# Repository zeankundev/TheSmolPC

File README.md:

# The Smol PC
An obscure, RP2350B-based computer motherboard on a smol form factor that you will think it's cute. And another absurd project I'm working on.

In essence, it's basically Adafruit's Fruit Jam but better and improved (fixes major issues lol, adafruit pls fix ur routing)

## Features
- [x] USB 1.1 with both power & data, up to 2x USB-A ports and 1x USB-C port, HID-compliant
- [x] SD Card as storage medium
- [x] HDMI/DVI video output
- [x] Big amount of flash and PSRAM (flash will be around 16MB) for a microcontroller
- [x] I2S/PCM audio output via a standard 3.5mm jack
- [ ] **Out of the box firmware boot** - this means that you can run any UEFI-like firmware for any OS you want to run, or you can use a stock firmware, or flash a generic firmware as if you were flashing on a normal RP2350 (maybe ?)
- [x] Debug Probe-compatible debug ports (Raspberry Pi Debug Probe)
- [x] Built-in WiFi support (ESP32-C3)

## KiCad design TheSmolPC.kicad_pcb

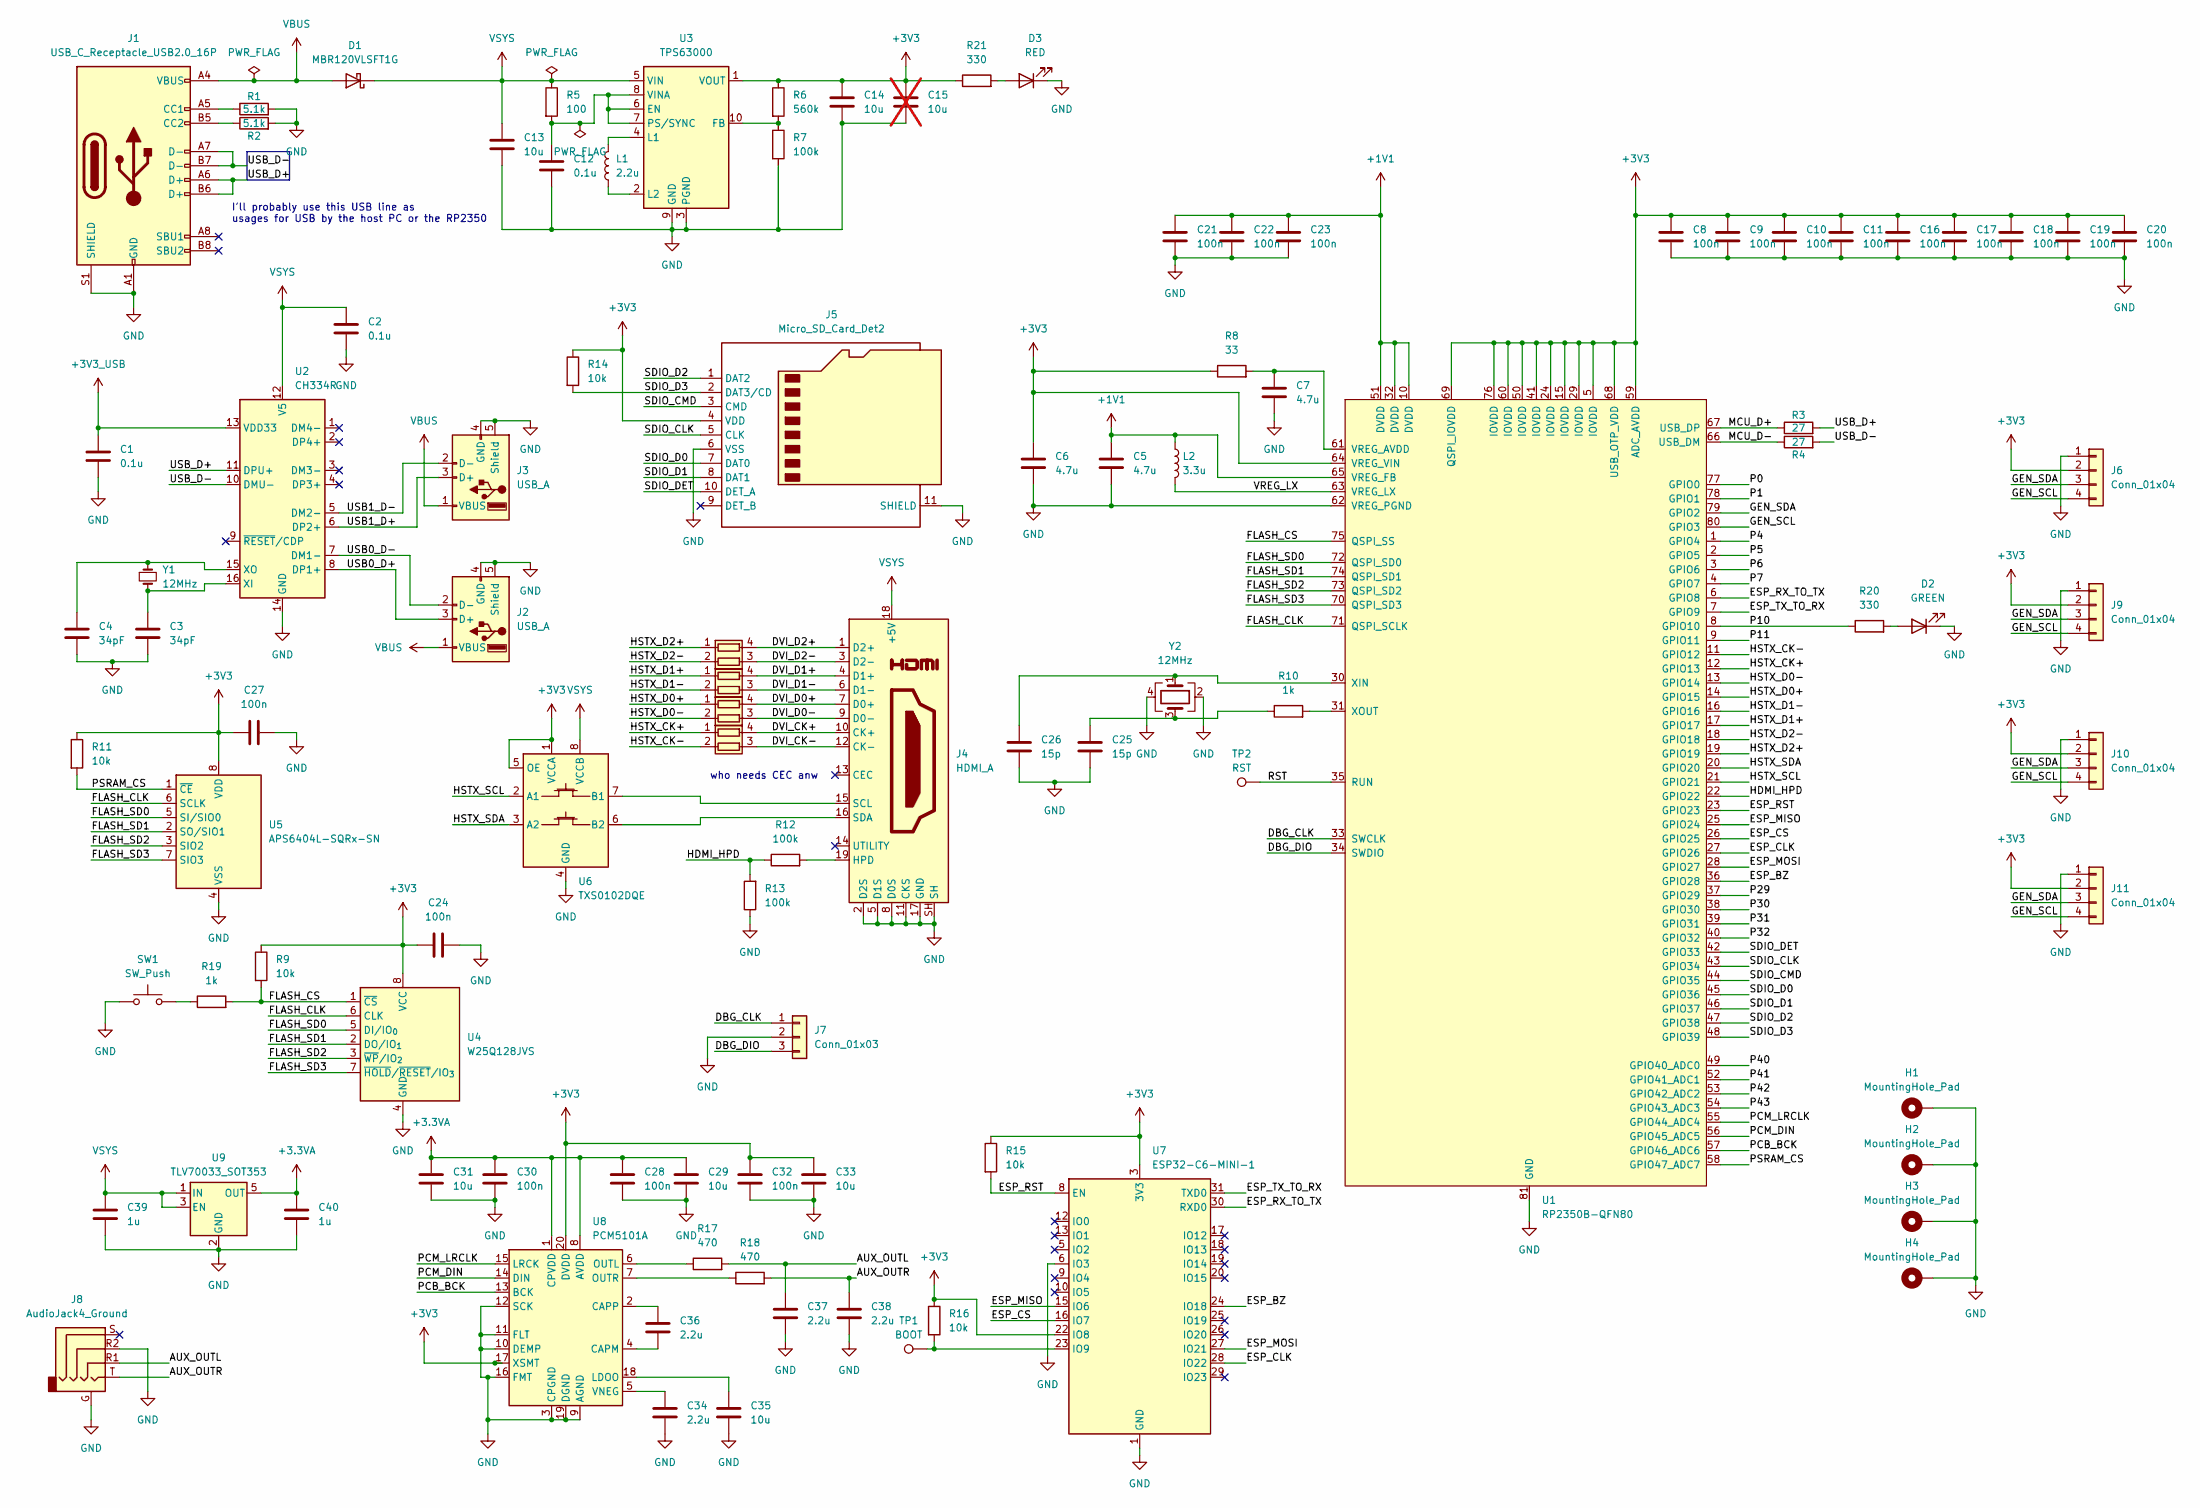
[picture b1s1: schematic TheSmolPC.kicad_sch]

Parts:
C1, C2, C12: 0.1u; C_0402_1005Metric
C3, C4: 34pF; C_0402_1005Metric
C5, C6, C7: 4.7u; C_0402_1005Metric
C8, C9, C10, C11, C16, C17, C18, C19, C20, C21, C22, C23, C24, C27, C28, C30, C32: 100n; C_0402_1005Metric
C13, C14: 10u; C_0805_2012Metric
C15: 10u; C_0805_2012Metric; not fitted
C25, C26: 15p; C_0402_1005Metric
C29, C31, C33, C35: 10u; C_0402_1005Metric
C34, C36, C37, C38: 2.2u; C_0402_1005Metric
C39, C40: 1u; C_0402_1005Metric
D1: MBR120VLSFT1G; D_SOD-123F
D2: GREEN; LED_0402_1005Metric
D3: RED; LED_0402_1005Metric
H1, H2, H3, H4: MountingHole_Pad; MountingHole_3.2mm_M3_DIN965_Pad
J1: USB_C_Receptacle_USB2.0_16P; USB_C_Receptacle_GCT_USB4105-xx-A_16P_TopMnt_Horizontal
J2, J3: USB_A; USB_A_Receptacle_GCT_USB1046
J4: HDMI_A; HDMI_A_Molex_208658-1001_Horizontal
J5: Micro_SD_Card_Det2; microSD_HC_Hirose_DM3D-SF
J6, J9, J10, J11: Conn_01x04; JST_SH_SM04B-SRSS-TB_1x04-1MP_P1.00mm_Horizontal
J7: Conn_01x03; JST_SH_SM03B-SRSS-TB_1x03-1MP_P1.00mm_Horizontal
J8: AudioJack4_Ground; Jack_3.5mm_KoreanHropartsElec_PJ-320D-4A_Horizontal
L1: 2.2u; L_Changjiang_FNR3015S
L2: 3.3u; L_Murata_DFE201610P
R1, R2: 5.1k; R_0402_1005Metric
R3, R4: 27; R_0402_1005Metric
R5: 100; R_0402_1005Metric
R6: 560k; R_0402_1005Metric
R7, R12, R13: 100k; R_0402_1005Metric
R8: 33; R_0402_1005Metric
R9, R11, R14, R15, R16: 10k; R_0402_1005Metric
R10, R19: 1k; R_0402_1005Metric
R17, R18: 470; R_0402_1005Metric
R20, R21: 330; R_0402_1005Metric
RN1, RN2, RN3, RN4: 220; R_Array_Convex_2x0402
SW1: SW_Push; SW_Push_1P1T_NO_Vertical_Wuerth_434133025816
TP1: BOOT; TestPoint_Pad_D1.0mm
TP2: RST; TestPoint_Pad_D1.0mm
U1: RP2350B-QFN80; QFN-80-1EP_10x10mm_P0.4mm_EP3.4x3.4mm_ThermalVias
U2: CH334R; QSOP-16_3.9x4.9mm_P0.635mm
U3: TPS63000; Texas_DRC0010J_ThermalVias
U4: W25Q128JVS; SOIC-8_5.3x5.3mm_P1.27mm
U5: APS6404L-SQRx-SN; SOIC-8_3.9x4.9mm_P1.27mm
U6: TXS0102DQE; X2SON-8_1.4x1mm_P0.35mm
U7: ESP32-C6-MINI-1
U8: PCM5101A; TSSOP-20_4.4x6.5mm_P0.65mm
U9: TLV70033_SOT353; SOT-353_SC-70-5
Y1: 12MHz; Crystal_SMD_Abracon_ABM3-2Pin_5.0x3.2mm
Y2: 12MHz; Crystal_SMD_3225-4Pin_3.2x2.5mm

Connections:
+1V1: C5.1, C21.1, C22.1, C23.1, L2.1, U1.10 (DVDD), U1.32 (DVDD), U1.51 (DVDD), U1.65 (VREG_FB)
+3.3VA: C28.1, C29.1, C30.1, C31.1, C40.1, U8.1 (CPVDD), U8.8 (AVDD), U9.5 (OUT)
+3V3: C6.1, C8.1, C9.1, C10.1, C11.1, C14.1, C15.1, C16.1, C17.1, C18.1, C19.1, C20.1, C24.1, C27.1, C32.1, C33.1, J5.4 (VDD), J6.2, J9.2, J10.2, J11.2, R6.1, R8.1, R9.1, R11.1, R14.1, R15.1, R16.1, R21.1, U1.5 (IOVDD), U1.15 (IOVDD), U1.24 (IOVDD), U1.29 (IOVDD), U1.41 (IOVDD), U1.50 (IOVDD), U1.59 (ADC_AVDD), U1.60 (IOVDD), U1.64 (VREG_VIN), U1.68 (USB_OTP_VDD), U1.69 (QSPI_IOVDD), U1.76 (IOVDD), U3.1 (VOUT), U4.8 (VCC), U5.8 (VDD), U6.1 (VCCA), U6.5 (OE), U7.3 (3V3), U7.22 (IO8), U8.17 (XSMT), U8.20 (DVDD)
+3V3_USB: C1.1, U2.13 (VDD33)
/AUX_OUTL: C37.1, J8.R1, R17.2
/AUX_OUTR: C38.1, J8.T, R18.2
/DBG_CLK: J7.1, U1.33 (SWCLK)
/DBG_DIO: J7.3, U1.34 (SWDIO)
/DVI_CK+: J4.10 (CK+), RN4.4 (R1.2)
/DVI_CK-: J4.12 (CK-), RN4.3 (R2.2)
/DVI_D0+: J4.7 (D0+), RN3.4 (R1.2)
/DVI_D0-: J4.9 (D0-), RN3.3 (R2.2)
/DVI_D1+: J4.4 (D1+), RN2.4 (R1.2)
/DVI_D1-: J4.6 (D1-), RN2.3 (R2.2)
/DVI_D2+: J4.1 (D2+), RN1.4 (R1.2)
/DVI_D2-: J4.3 (D2-), RN1.3 (R2.2)
/ESP_BZ: U1.36 (GPIO28), U7.24 (IO18)
/ESP_CLK: U1.27 (GPIO26), U7.28 (IO22)
/ESP_CS: U1.26 (GPIO25), U7.16 (IO7)
/ESP_MISO: U1.25 (GPIO24), U7.15 (IO6)
/ESP_MOSI: U1.28 (GPIO27), U7.27 (IO21)
/ESP_RST: R15.2, U1.23 (GPIO23), U7.8 (EN)
/ESP_RX_TO_TX: U1.6 (GPIO8), U7.30 (RXD0)
/ESP_TX_TO_RX: U1.7 (GPIO9), U7.31 (TXD0)
/FLASH_CLK: U1.71 (QSPI_SCLK), U4.6 (CLK), U5.6 (SCLK)
/FLASH_CS: R9.2, R19.2, U1.75 (QSPI_SS), U4.1 (~CS)
/FLASH_SD0: U1.72 (QSPI_SD0), U4.5 (DI/IO_{0}), U5.5 (SI/SIO0)
/FLASH_SD1: U1.74 (QSPI_SD1), U4.2 (DO/IO_{1}), U5.2 (SO/SIO1)
/FLASH_SD2: U1.73 (QSPI_SD2), U4.3 (~WP/IO_{2}), U5.3 (SIO2)
/FLASH_SD3: U1.70 (QSPI_SD3), U4.7 (~HOLD/~RESET/IO_{3}), U5.7 (SIO3)
/GEN_SCL: J6.4, J9.4, J10.4, J11.4, U1.80 (GPIO3)
/GEN_SDA: J6.3, J9.3, J10.3, J11.3, U1.79 (GPIO2)
/HDMI_HPD: R12.1, R13.2, U1.22 (GPIO22)
/HSTX_CK+: RN4.1 (R1.1), U1.12 (GPIO13)
/HSTX_CK-: RN4.2 (R2.1), U1.11 (GPIO12)
/HSTX_D0+: RN3.1 (R1.1), U1.14 (GPIO15)
/HSTX_D0-: RN3.2 (R2.1), U1.13 (GPIO14)
/HSTX_D1+: RN2.1 (R1.1), U1.17 (GPIO17)
/HSTX_D1-: RN2.2 (R2.1), U1.16 (GPIO16)
/HSTX_D2+: RN1.1 (R1.1), U1.19 (GPIO19)
/HSTX_D2-: RN1.2 (R2.1), U1.18 (GPIO18)
/HSTX_SCL: U1.21 (GPIO21), U6.2 (A1)
/HSTX_SDA: U1.20 (GPIO20), U6.3 (A2)
/MCU_D+: R3.1, U1.67 (USB_DP)
/MCU_D-: R4.1, U1.66 (USB_DM)
/P0: U1.77 (GPIO0)
/P1: U1.78 (GPIO1)
/P4: U1.1 (GPIO4)
/P5: U1.2 (GPIO5)
/P6: U1.3 (GPIO6)
/P7: U1.4 (GPIO7)
/P10: R20.1, U1.8 (GPIO10)
/P11: U1.9 (GPIO11)
/P29: U1.37 (GPIO29)
/P30: U1.38 (GPIO30)
/P31: U1.39 (GPIO31)
/P32: U1.40 (GPIO32)
/P40: U1.49 (GPIO40_ADC0)
/P41: U1.52 (GPIO41_ADC1)
/P42: U1.53 (GPIO42_ADC2)
/P43: U1.54 (GPIO43_ADC3)
/PCB_BCK: U1.57 (GPIO46_ADC6), U8.13 (BCK)
/PCM_DIN: U1.56 (GPIO45_ADC5), U8.14 (DIN)
/PCM_LRCLK: U1.55 (GPIO44_ADC4), U8.15 (LRCK)
/PSRAM_CS: R11.2, U1.58 (GPIO47_ADC7), U5.1 (~CE)
/RST: TP2.1, U1.35 (RUN)
/SDIO_CLK: J5.5 (CLK), U1.43 (GPIO34)
/SDIO_CMD: J5.3 (CMD), U1.44 (GPIO35)
/SDIO_D0: J5.7 (DAT0), U1.45 (GPIO36)
/SDIO_D1: J5.8 (DAT1), U1.46 (GPIO37)
/SDIO_D2: J5.1 (DAT2), U1.47 (GPIO38)
/SDIO_D3: J5.2 (DAT3/CD), R14.2, U1.48 (GPIO39)
/SDIO_DET: J5.10 (DET_A), U1.42 (GPIO33)
/USB0_D+: J2.3 (D+), U2.8 (DP1+)
/USB0_D-: J2.2 (D-), U2.7 (DM1-)
/USB1_D+: J3.3 (D+), U2.6 (DP2+)
/USB1_D-: J3.2 (D-), U2.5 (DM2-)
/USB_D+: J1.A6 (D+), J1.B6 (D+), R3.2, U2.11 (DPU+)
/USB_D-: J1.A7 (D-), J1.B7 (D-), R4.2, U2.10 (DMU-)
/VREG_LX: L2.2, U1.63 (VREG_LX)
GND: C1.2, C2.2, C3.2, C4.2, C5.2, C6.2, C7.2, C8.2, C9.2, C10.2, C11.2, C12.2, C13.2, C14.2, C15.2, C16.2, C17.2, C18.2, C19.2, C20.2, C21.2, C22.2, C23.2, C24.2, C25.2, C26.2, C27.2, C28.2, C29.2, C30.2, C31.2, C32.2, C33.2, C34.2, C35.2, C37.2, C38.2, C39.2, C40.2, D2.1 (K), D3.1 (K), H1.1, H2.1, H3.1, H4.1, J1.A1 (GND), J1.A12 (GND), J1.B1 (GND), J1.B12 (GND), J1.S1 (SHIELD), J2.4 (GND), J2.5 (Shield), J3.4 (GND), J3.5 (Shield), J4.2 (D2S), J4.5 (D1S), J4.8 (D0S), J4.11 (CKS), J4.17 (GND), J4.SH, J5.6 (VSS), J5.11 (SHIELD), J6.1, J7.2, J8.G, J8.R2, J9.1, J10.1, J11.1, R1.2, R2.2, R7.2, R13.1, SW1.1, U1.62 (VREG_PGND), U1.81 (GND), U2.14 (GND), U3.3 (PGND), U3.9 (GND), U3.11 (PGND), U4.4 (GND), U5.4 (VSS), U6.4 (GND), U7.1 (GND), U7.2 (GND), U7.6 (IO3), U7.11 (GND), U7.14 (GND), U7.36 (GND), U7.37 (GND), U7.38 (GND), U7.39 (GND), U7.40 (GND), U7.41 (GND), U7.42 (GND), U7.43 (GND), U7.44 (GND), U7.45 (GND), U7.46 (GND), U7.47 (GND), U7.48 (GND), U7.49 (GND), U7.50 (GND), U7.51 (GND), U7.52 (GND), U7.53 (GND), U8.3 (CPGND), U8.9 (AGND), U8.10 (DEMP), U8.11 (FLT), U8.12 (SCK), U8.16 (FMT), U8.19 (DGND), U9.2 (GND), Y2.2, Y2.4
unnamed: C25.1, R10.1, Y2.3
unnamed: D2.2 (A), R20.2
unnamed: D3.2 (A), R21.2
unnamed: J1.A5 (CC1), R1.1
unnamed: J1.B5 (CC2), R2.1
unnamed: J4.19 (HPD), R12.2
unnamed: J4.15 (SCL), U6.7 (B1)
unnamed: J4.16 (SDA), U6.6 (B2)
unnamed: R19.1, SW1.2
unnamed: C7.1, R8.2, U1.61 (VREG_AVDD)
unnamed: C26.1, U1.30 (XIN), Y2.1
unnamed: R10.2, U1.31 (XOUT)
unnamed: C3.1, U2.16 (XI), Y1.2
unnamed: C4.1, U2.15 (XO), Y1.1
unnamed: C12.1, R5.2, U3.6 (EN), U3.7 (PS/SYNC), U3.8 (VINA)
unnamed: R6.2, R7.1, U3.10 (FB)
unnamed: L1.2, U3.4 (L1)
unnamed: L1.1, U3.2 (L2)
unnamed: R16.2, TP1.1, U7.23 (IO9)
unnamed: C36.2, U8.4 (CAPM)
unnamed: C36.1, U8.2 (CAPP)
unnamed: C35.1, U8.18 (LDOO)
unnamed: R17.1, U8.6 (OUTL)
unnamed: R18.1, U8.7 (OUTR)
unnamed: C34.1, U8.5 (VNEG)
VBUS: D1.2 (A), J1.A4 (VBUS), J1.A9 (VBUS), J1.B4 (VBUS), J1.B9 (VBUS), J2.1 (VBUS), J3.1 (VBUS)
VSYS: C2.1, C13.1, C39.1, D1.1 (K), J4.18 (+5V), R5.1, U2.12 (V5), U3.5 (VIN), U6.8 (VCCB), U9.1 (IN), U9.3 (EN)

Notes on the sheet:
who needs CEC anw
I'll probably use this USB line as usages for USB by the host PC or the RP2350

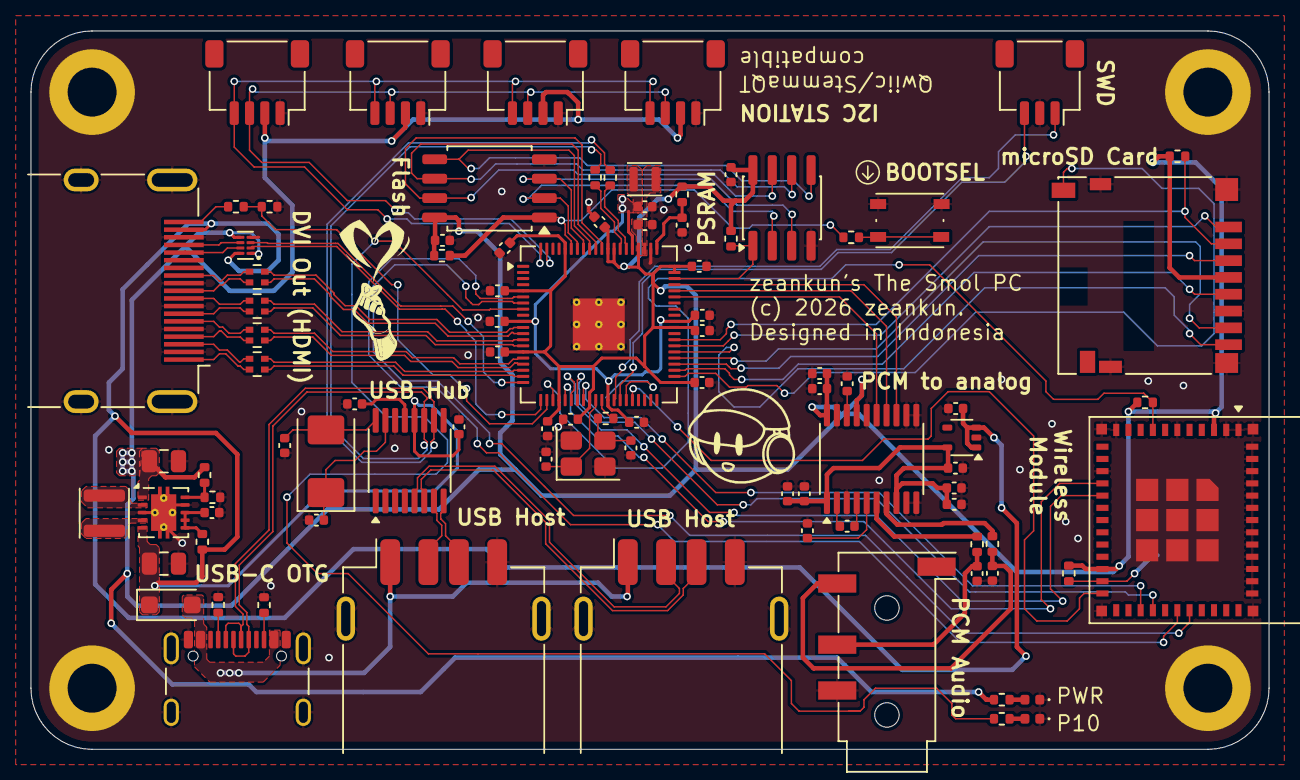
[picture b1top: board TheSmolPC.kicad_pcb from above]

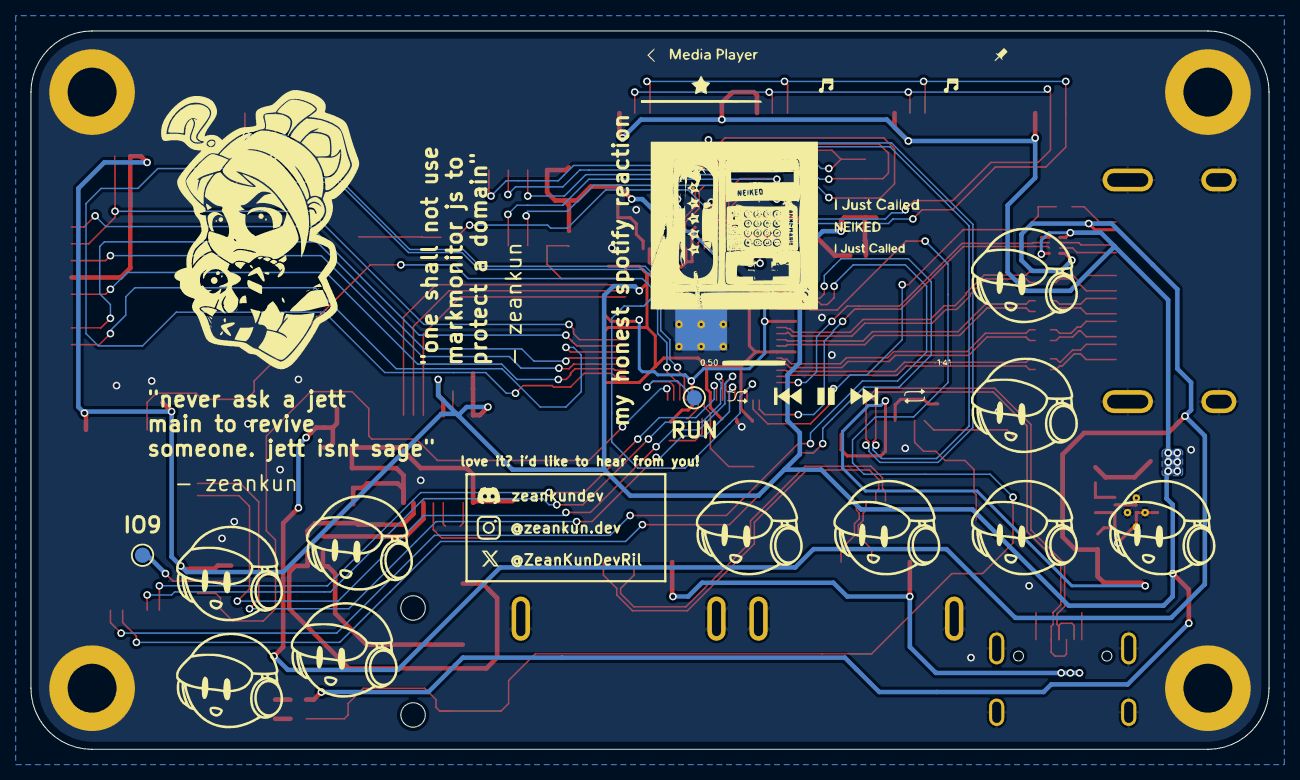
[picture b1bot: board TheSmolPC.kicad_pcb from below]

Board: 2 copper layers, 81.0 x 47.0 mm, 98 parts (2 on the bottom side), 93 nets.

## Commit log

2025-10-08 add readme
2025-10-08 woopsies
2025-10-16 just some project mods
2025-10-16 add more thingies yay
2025-10-16 added new symlib tables
2025-10-18 partially finished the schematic ig
2025-10-18 fixed the schematic differential pair polarities (tested with the pcb editor)
2025-11-08 recompleting the schema so now its full
2025-11-08 finalizing schema (some still wip and will be changed dynamically
2025-11-13 pcb finally finished

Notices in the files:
TheSmolPC.kicad_pcb:
(c) 2026 zeankun.
